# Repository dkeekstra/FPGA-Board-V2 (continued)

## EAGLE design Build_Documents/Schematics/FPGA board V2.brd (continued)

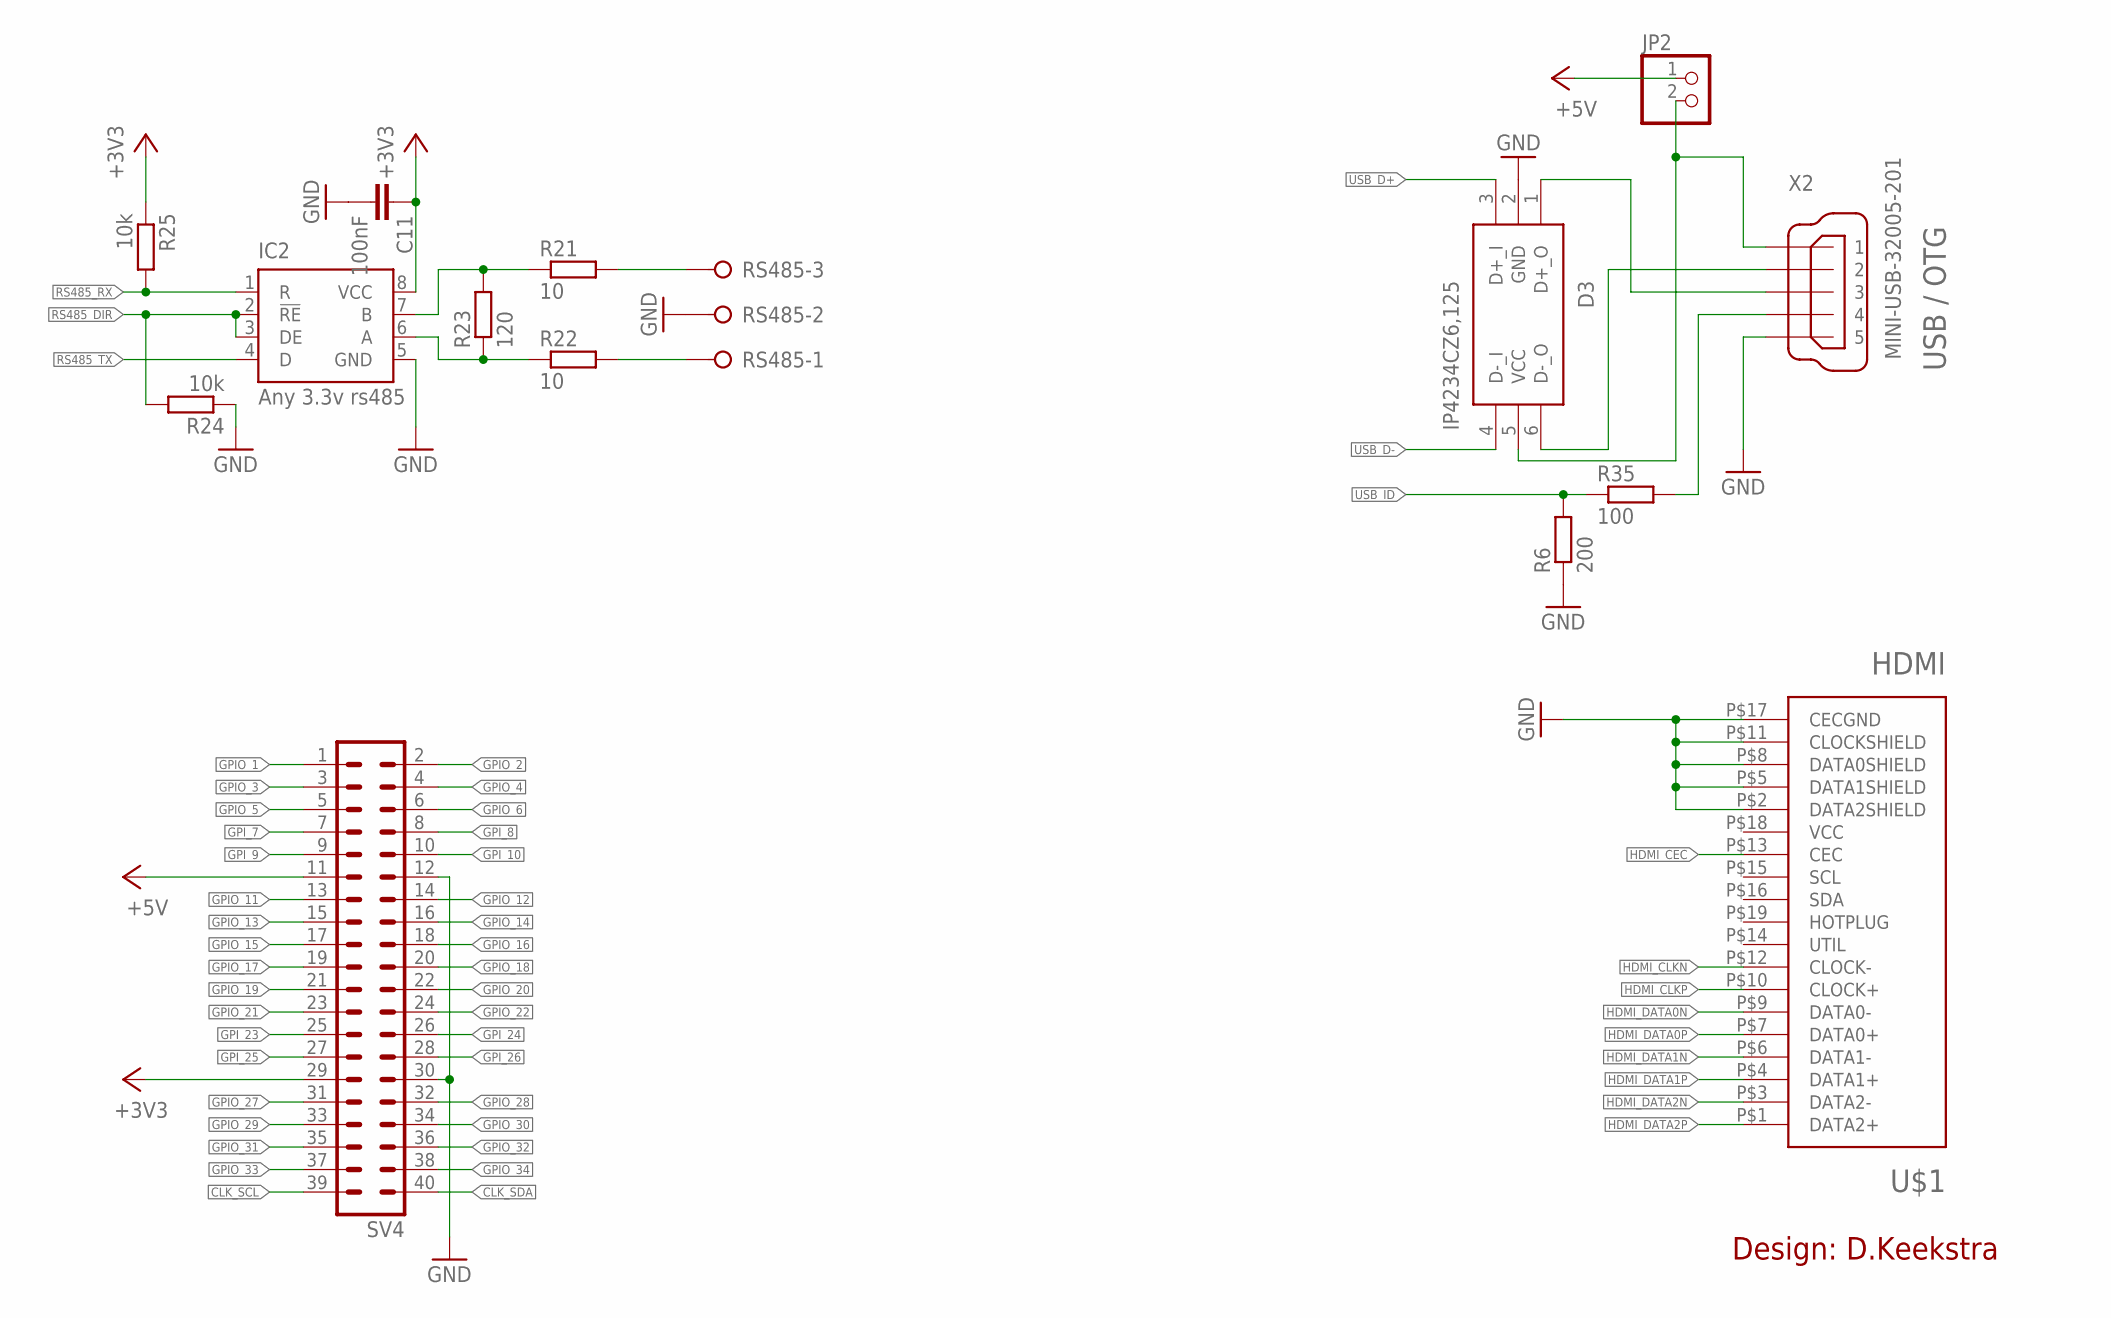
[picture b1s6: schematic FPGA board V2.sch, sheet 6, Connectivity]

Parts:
C11: 100nF; C0603
D3: IP4234CZ6,125; SOT95P275X110-6N
IC2: Any 3.3v rs485; SO-08
JP2: PINHD-1X2; 1X02
R6: 200; R0603
R21, R22: 10; R0603
R23: 120; R0603
R24, R25: 10k; R0603
R35: 100; R0603
RS485: W237-3E
SV4: MA20-2
U$1: HDMI; HDMI_A
X2: MINI-USB-32005-201; 32005-201

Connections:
+3V3: C11.1, IC2.8 (VCC), R25.1, SV4.29; also elsewhere on the board
+5V: JP2.1, SV4.11; also elsewhere on the board
CLK_SCL: SV4.39; also elsewhere on the board
CLK_SDA: SV4.40; also elsewhere on the board
GND: C11.2, D3.2 (GND), IC2.5 (GND), R6.1, R24.1, RS485.2, SV4.12, SV4.30, U$1.P$2 (DATA2SHIELD), U$1.P$5 (DATA1SHIELD), U$1.P$8 (DATA0SHIELD), U$1.P$11 (CLOCKSHIELD), U$1.P$17 (CECGND), X2.5; also elsewhere on the board
GPIO_1: SV4.1; also elsewhere on the board
GPIO_2: SV4.2; also elsewhere on the board
GPIO_3: SV4.3; also elsewhere on the board
GPIO_4: SV4.4; also elsewhere on the board
GPIO_5: SV4.5; also elsewhere on the board
GPIO_6: SV4.6; also elsewhere on the board
GPIO_11: SV4.13; also elsewhere on the board
GPIO_12: SV4.14; also elsewhere on the board
GPIO_13: SV4.15; also elsewhere on the board
GPIO_14: SV4.16; also elsewhere on the board
GPIO_15: SV4.17; also elsewhere on the board
GPIO_16: SV4.18; also elsewhere on the board
GPIO_17: SV4.19; also elsewhere on the board
GPIO_18: SV4.20; also elsewhere on the board
GPIO_19: SV4.21; also elsewhere on the board
GPIO_20: SV4.22; also elsewhere on the board
GPIO_21: SV4.23; also elsewhere on the board
GPIO_22: SV4.24; also elsewhere on the board
GPIO_27: SV4.31; also elsewhere on the board
GPIO_28: SV4.32; also elsewhere on the board
GPIO_29: SV4.33; also elsewhere on the board
GPIO_30: SV4.34; also elsewhere on the board
GPIO_31: SV4.35; also elsewhere on the board
GPIO_32: SV4.36; also elsewhere on the board
GPIO_33: SV4.37; also elsewhere on the board
GPIO_34: SV4.38; also elsewhere on the board
GPI_7: SV4.7; also elsewhere on the board
GPI_8: SV4.8; also elsewhere on the board
GPI_9: SV4.9; also elsewhere on the board
GPI_10: SV4.10; also elsewhere on the board
GPI_23: SV4.25; also elsewhere on the board
GPI_24: SV4.26; also elsewhere on the board
GPI_25: SV4.27; also elsewhere on the board
GPI_26: SV4.28; also elsewhere on the board
HDMI_CEC: U$1.P$13 (CEC); also elsewhere on the board
HDMI_CLKN: U$1.P$12 (CLOCK-); also elsewhere on the board
HDMI_CLKP: U$1.P$10 (CLOCK+); also elsewhere on the board
HDMI_DATA0N: U$1.P$9 (DATA0-); also elsewhere on the board
HDMI_DATA0P: U$1.P$7 (DATA0+); also elsewhere on the board
HDMI_DATA1N: U$1.P$6 (DATA1-); also elsewhere on the board
HDMI_DATA1P: U$1.P$4 (DATA1+); also elsewhere on the board
HDMI_DATA2N: U$1.P$3 (DATA2-); also elsewhere on the board
HDMI_DATA2P: U$1.P$1 (DATA2+); also elsewhere on the board
unnamed: D3.6 (D-_O), X2.2
unnamed: D3.1 (D+_O), X2.3
unnamed: D3.5 (VCC), JP2.2, X2.1
unnamed: IC2.7 (B), R21.1, R23.2
unnamed: IC2.6 (A), R22.1, R23.1
unnamed: R22.2, RS485.1
unnamed: R21.2, RS485.3
unnamed: R35.2, X2.4
RS485_DIR: IC2.2 (!RE), IC2.3 (DE), R24.2; also elsewhere on the board
RS485_RX: IC2.1 (R), R25.2; also elsewhere on the board
RS485_TX: IC2.4 (D); also elsewhere on the board
USB_D+: D3.3 (D+_I); also elsewhere on the board
USB_D-: D3.4 (D-_I); also elsewhere on the board
USB_ID: R6.2, R35.1; also elsewhere on the board

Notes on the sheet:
USB / OTG
Design: D.Keekstra

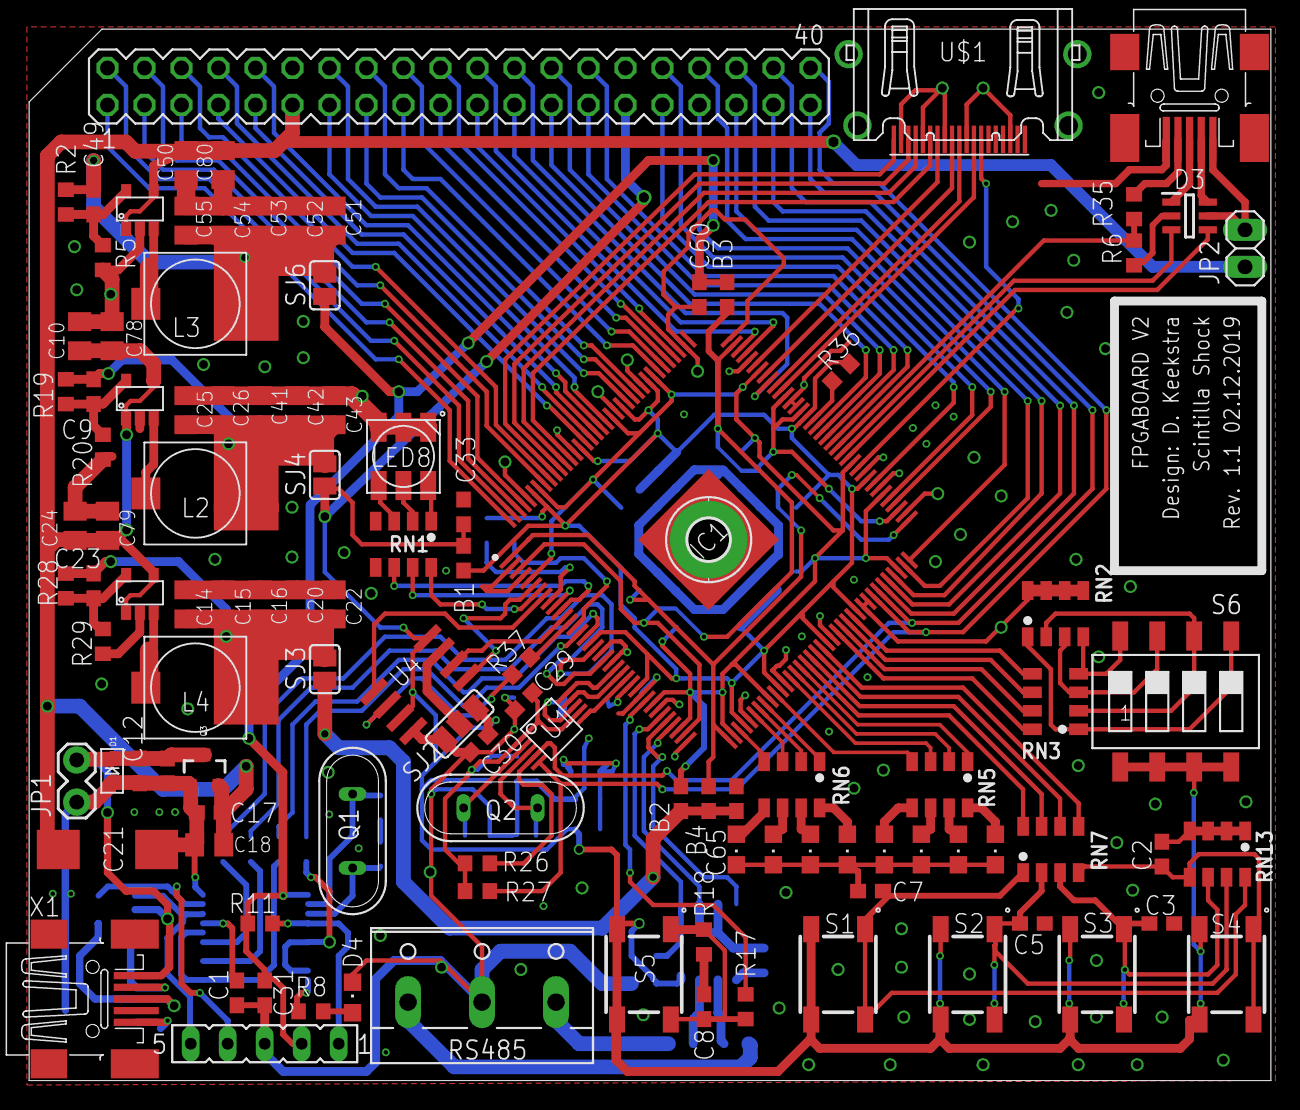
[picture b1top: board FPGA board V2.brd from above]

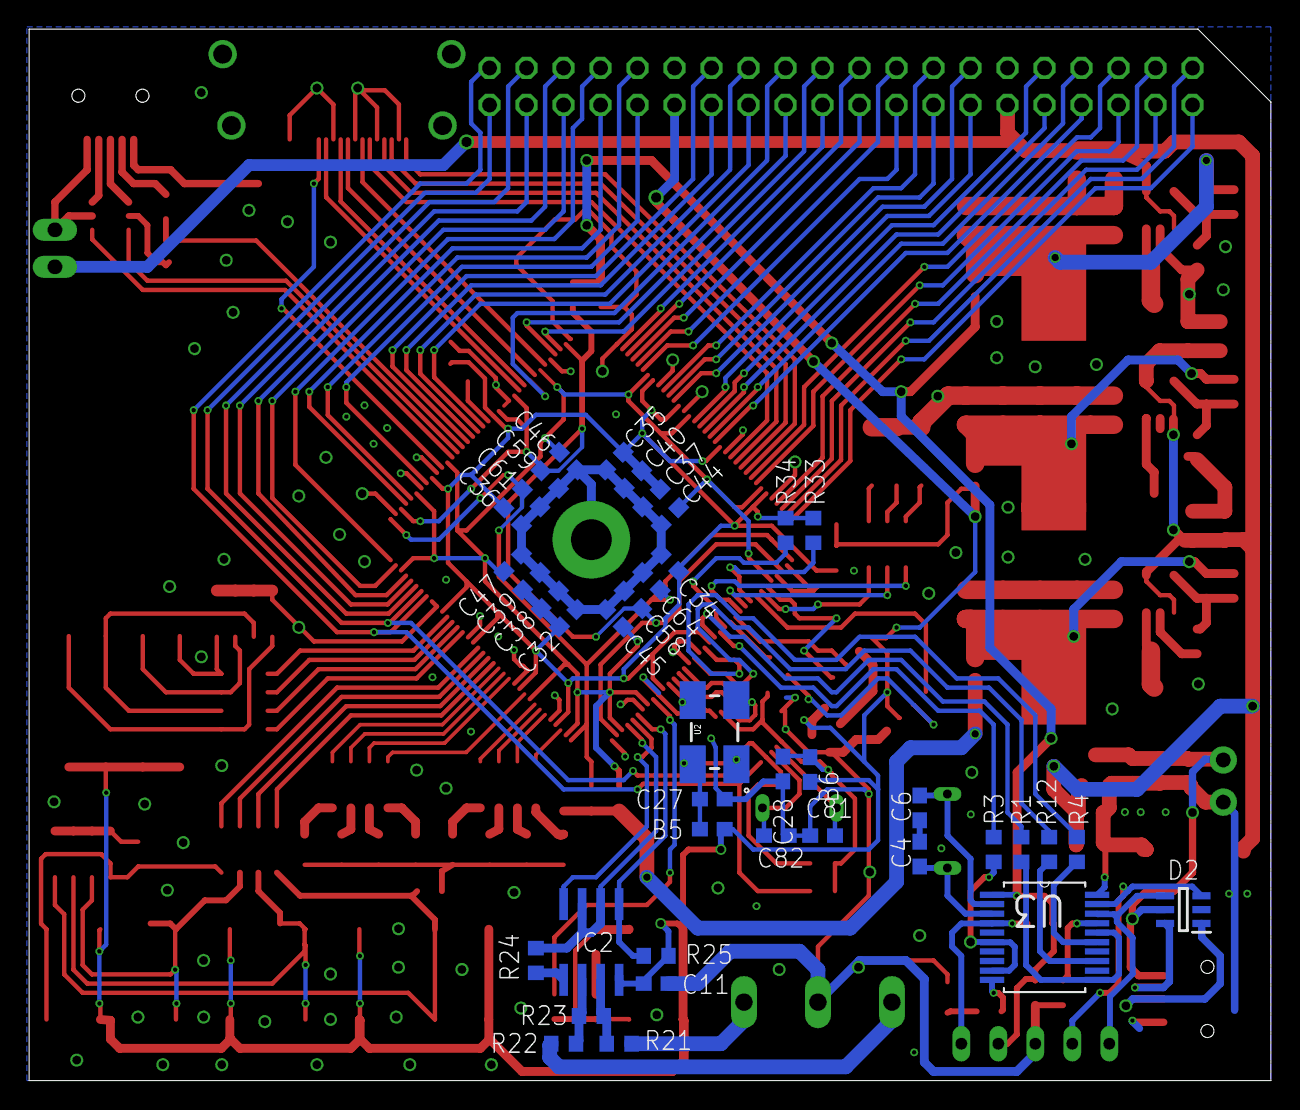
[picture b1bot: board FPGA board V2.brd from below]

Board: 2 copper layers, 85.3 x 72.2 mm, 151 parts (40 on the bottom side), 153 nets.

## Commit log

2019-12-10 Initial
2019-12-10 Update Front page
2019-12-10 Make a list
2019-12-10 Add image of the board
2019-12-10 Add image
2019-12-10 remove space
2019-12-10 Update bom
2019-12-10 Build instruction
2019-12-10 Update build instruction for xtals
2019-12-10 Print partlist
2019-12-17 Add demo software
2019-12-17 Set theme jekyll-theme-minimal
2019-12-19 demosoftware edited by Bert Molenkamp
    removed the synopsys (non-IEEE libraries): std_logic_arith and std_logic_unsigned
    in "case sws is" you alread know that sws(0) is '1' so with that information rgbc<=ses(3 downto 1)
    increment of rgbc can be replaced with MOD 2**length
    same for bugc
2019-12-19 Add jic file for flash programming
2020-02-04 add bead 5 and 6 in build instruction
2020-02-04 update instructions
2020-02-05 update the build instructions
2020-02-12 update picture
